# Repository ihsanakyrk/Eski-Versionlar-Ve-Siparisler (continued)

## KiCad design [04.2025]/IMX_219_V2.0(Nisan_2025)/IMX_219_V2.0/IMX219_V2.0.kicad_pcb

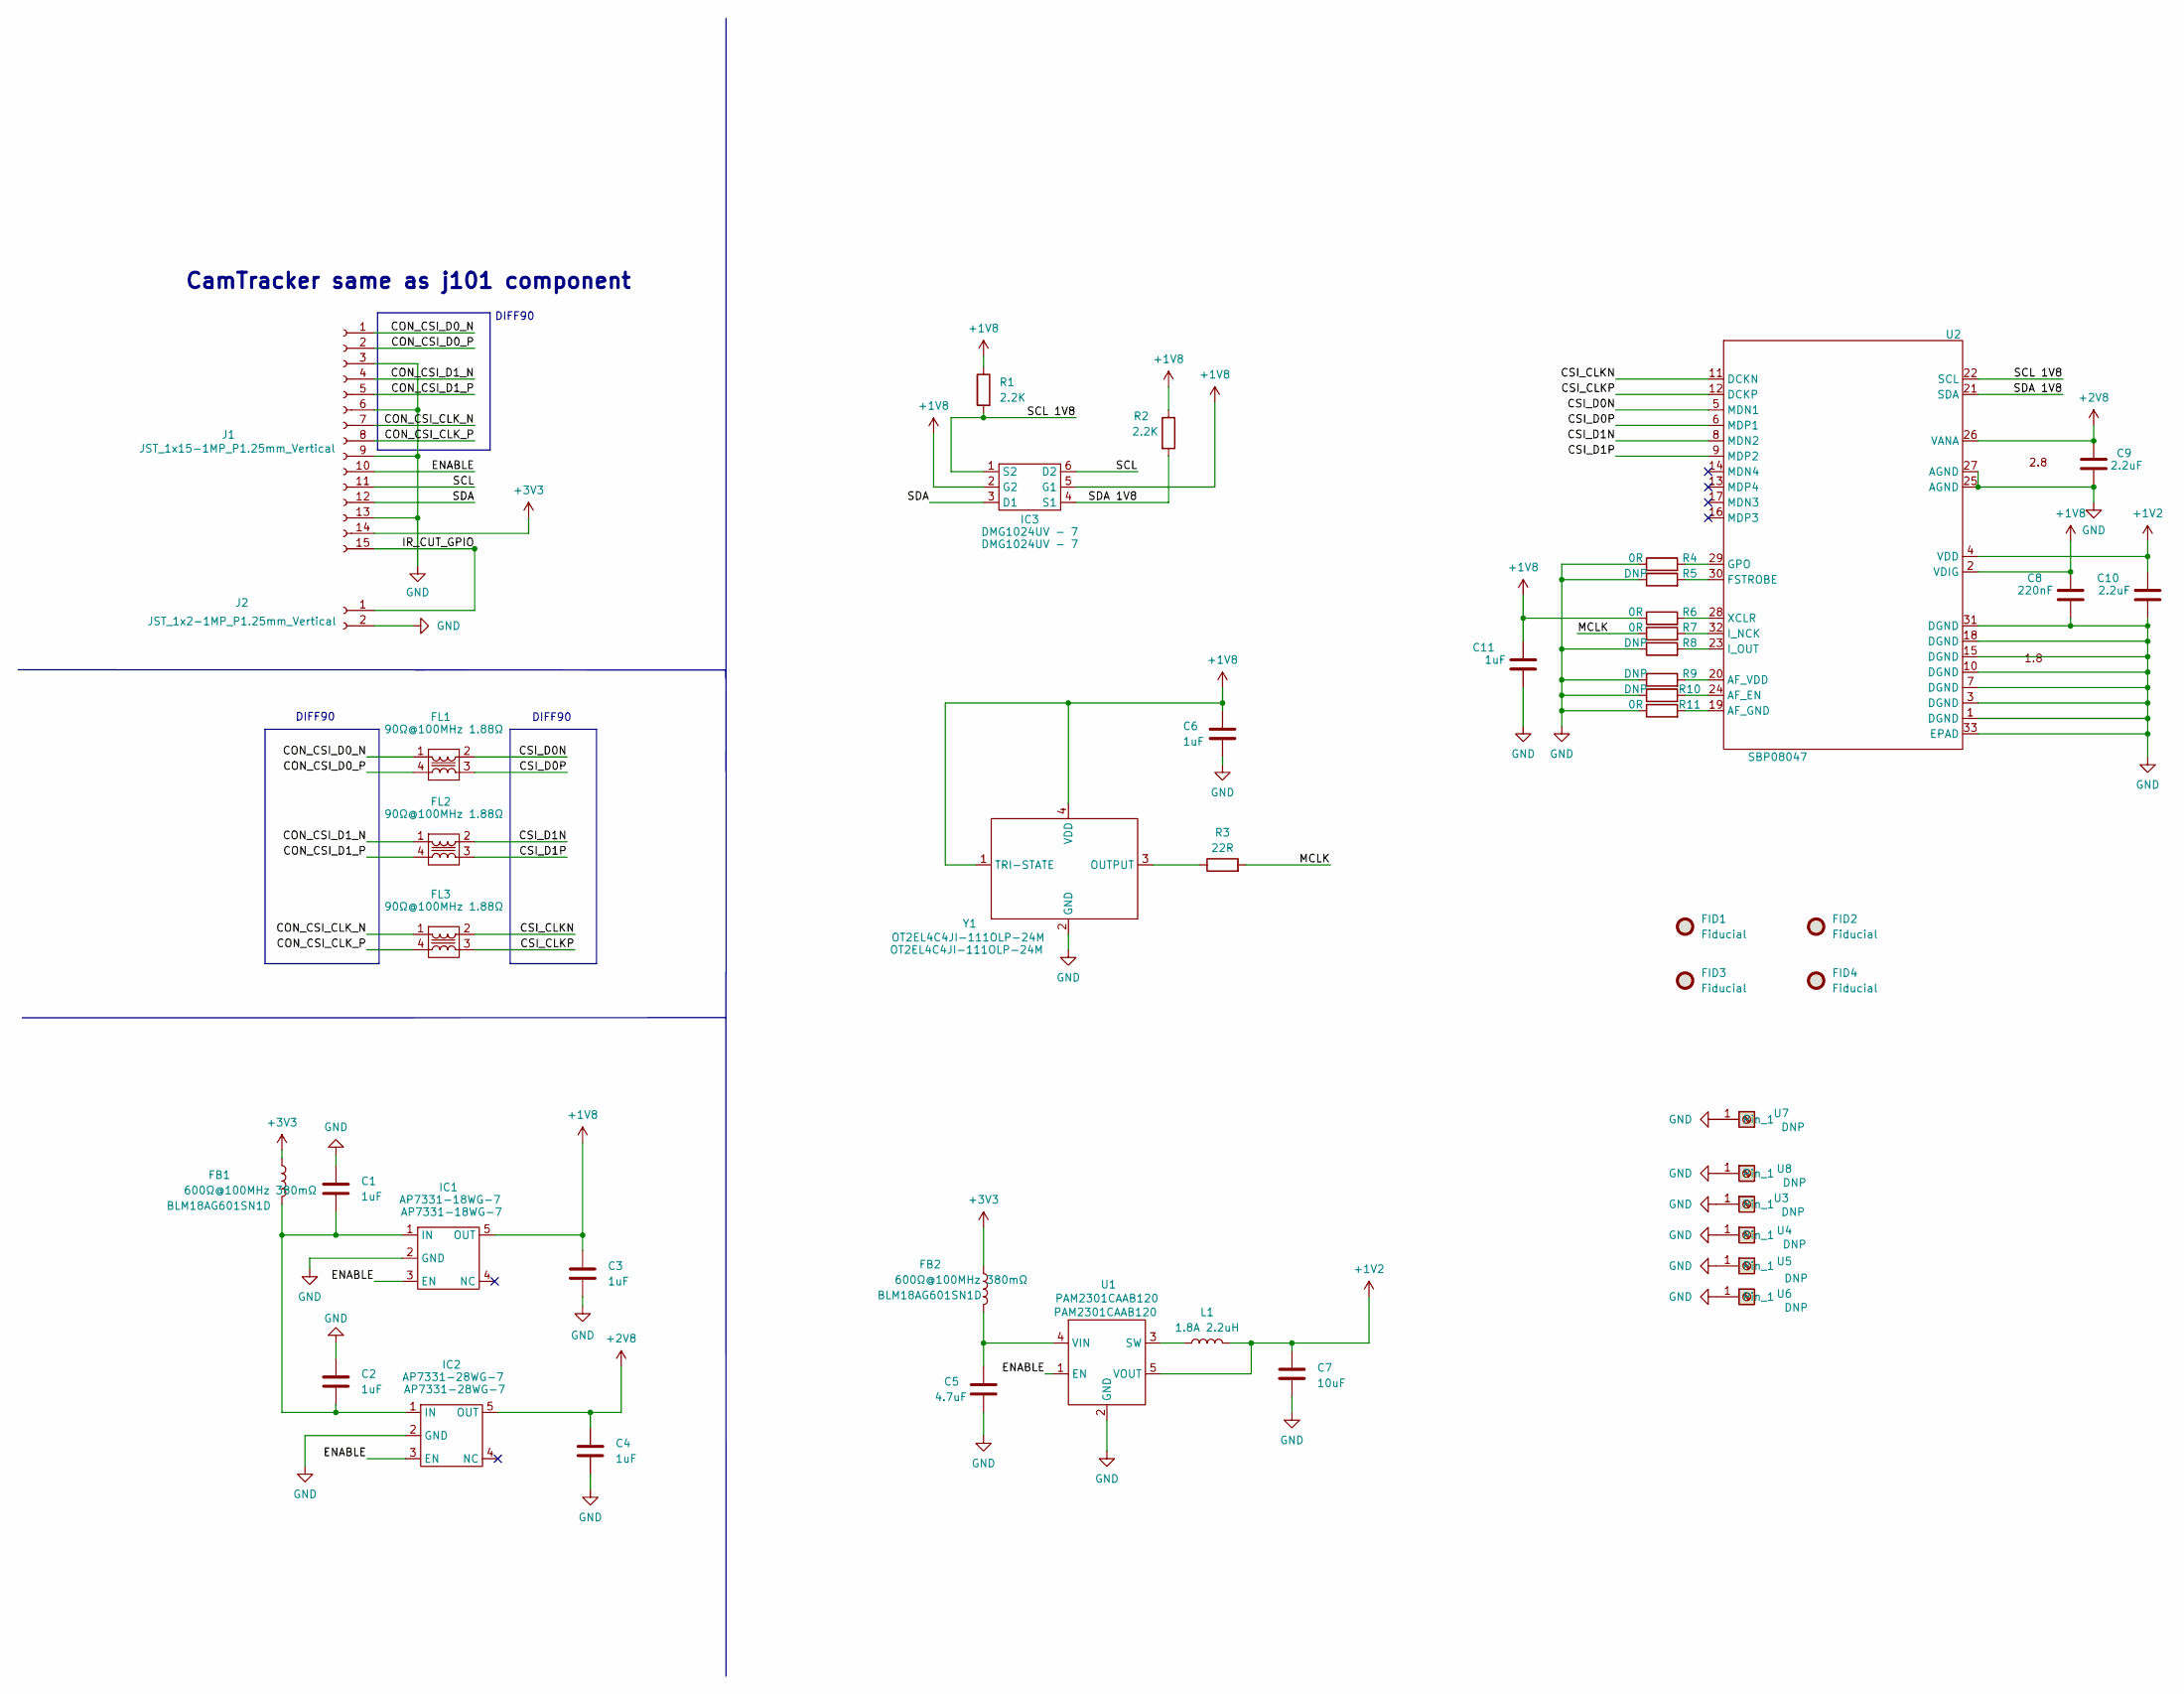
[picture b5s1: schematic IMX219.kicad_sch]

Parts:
C1, C2, C3, C4, C6: 1uF; C_0402_1005Metric; MPN CL05A105KP5NNNC
C5: 4.7uF; C_0603_1608Metric; MPN CL10A475KO8NNNC
C7: 10uF; C_0805_2012Metric; MPN CL21A106KAYNNNE
C8: 220nF; C_0402_1005Metric; MPN 0402B224K160NT
C9, C10: 2.2uF; C_0402_1005Metric; MPN CL05A225MQ5NSNC
C11: 1uF; C_0402_1005Metric
FB1, FB2: 600Ω@100MHz 380mΩ; BLM18SP221SN1B; MPN BLM18AG601SN1D
FID1, FID2, FID3, FID4: Fiducial; Fiducial_0.5mm_Mask1mm
FL1, FL2, FL3: 90Ω@100MHz 1.88Ω; DLP11SN900HL2L; MPN DLP11SN900HL2L
IC1: AP7331-18WG-7; AP7331; MPN AP7331-18WG-7
IC2: AP7331-28WG-7; AP7331; MPN AP7331-28WG-7
IC3: DMG1024UV - 7; SOT-563; MPN DMG1024UV - 7
J1: JST_1x15-1MP_P1.25mm_Vertical; MPN 1.25mm间距 立贴 1*15p
J2: JST_1x2-1MP_P1.25mm_Vertical; Con_2Ways_1.25mm; MPN p=1.25 1*3p
L1: 1.8A 2.2uH; L_1008_2520Metric; MPN IFSC1008ABER2R2M01
R1, R2: 2.2K; R_0402_1005Metric; MPN 0402WGF2201TCE
R3: 22R; R_0402_1005Metric; MPN 0402WGF220JTCE
R4, R7: 0R; R_0402_1005Metric; MPN RC-02000FT
R5, R8, R9, R10: DNP; R_0402_1005Metric; MPN DNP
R6, R11: 0R; R_0402_1005Metric
U1: PAM2301CAAB120; SOT-23-5; MPN PAM2301CAAB120
U2: SBP08047; MPN SBP08047
U3, U4, U5, U6, U7, U8: DNP; Screw Terminal Shinbo_2; MPN DNP
Y1: OT2EL4C4JI-111OLP-24M; MPN OT2EL4C4JI-111OLP-24M

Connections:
+1V2: C7.1, C10.2, L1.2, U1.5 (VOUT), U2.4 (VDD)
+1V8: C3.1, C6.1, C8.2, C11.2, IC1.5 (OUT), IC3.2 (G2), IC3.5 (G1), R1.1, R2.1, R6.1, U2.2 (VDIG), Y1.1 (TRI-STATE), Y1.4 (VDD)
+2V8: C4.1, C9.2, IC2.5 (OUT), U2.26 (VANA)
+3V3: FB1.1, FB2.1, J1.14
/IMX219/CON_CSI_CLK_N: FL3.1, J1.7
/IMX219/CON_CSI_CLK_P: FL3.4, J1.8
/IMX219/CON_CSI_D0_N: FL1.1, J1.1
/IMX219/CON_CSI_D0_P: FL1.4, J1.2
/IMX219/CON_CSI_D1_N: FL2.1, J1.4
/IMX219/CON_CSI_D1_P: FL2.4, J1.5
/IMX219/CSI_CLKN: FL3.2, U2.11 (DCKN)
/IMX219/CSI_CLKP: FL3.3, U2.12 (DCKP)
/IMX219/CSI_D0N: FL1.2, U2.5 (MDN1)
/IMX219/CSI_D0P: FL1.3, U2.6 (MDP1)
/IMX219/CSI_D1N: FL2.2, U2.8 (MDN2)
/IMX219/CSI_D1P: FL2.3, U2.9 (MDP2)
/IMX219/ENABLE: IC1.3 (EN), IC2.3 (EN), J1.10, U1.1 (EN)
/IMX219/IR_CUT_GPIO: J1.15, J2.1
/IMX219/MCLK: R3.2, R7.1
/IMX219/SCL: IC3.6 (D2), J1.11
/IMX219/SCL 1V8: IC3.1 (S2), R1.2, U2.22 (SCL)
/IMX219/SDA: IC3.3 (D1), J1.12
/IMX219/SDA 1V8: IC3.4 (S1), R2.2, U2.21 (SDA)
GND: C1.1, C2.1, C3.2, C4.2, C5.2, C6.2, C7.2, C8.1, C9.1, C10.1, C11.1, IC1.2 (GND), IC2.2 (GND), J1.3, J1.6, J1.9, J1.13, J2.2, R4.1, R5.1, R8.1, R9.1, R10.1, R11.1, U1.2 (GND), U2.1 (DGND), U2.3 (DGND), U2.7 (DGND), U2.10 (DGND), U2.15 (DGND), U2.18 (DGND), U2.25 (AGND), U2.27 (AGND), U2.31 (DGND), U2.33 (EPAD), U3.1, U4.1, U5.1, U6.1, U7.1, U8.1, Y1.2 (GND)
unnamed: C1.2, C2.2, FB1.2, IC1.1 (IN), IC2.1 (IN)
unnamed: L1.1, U1.3 (SW)
unnamed: C5.1, FB2.2, U1.4 (VIN)
unnamed: R10.2, U2.24 (AF_EN)
unnamed: R11.2, U2.19 (AF_GND)
unnamed: R9.2, U2.20 (AF_VDD)
unnamed: R5.2, U2.30 (FSTROBE)
unnamed: R4.2, U2.29 (GPO)
unnamed: R7.2, U2.32 (I_NCK)
unnamed: R8.2, U2.23 (I_OUT)
unnamed: R6.2, U2.28 (XCLR)
unnamed: R3.1, Y1.3 (OUTPUT)

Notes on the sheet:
DIFF90
CamTracker same as j101 component

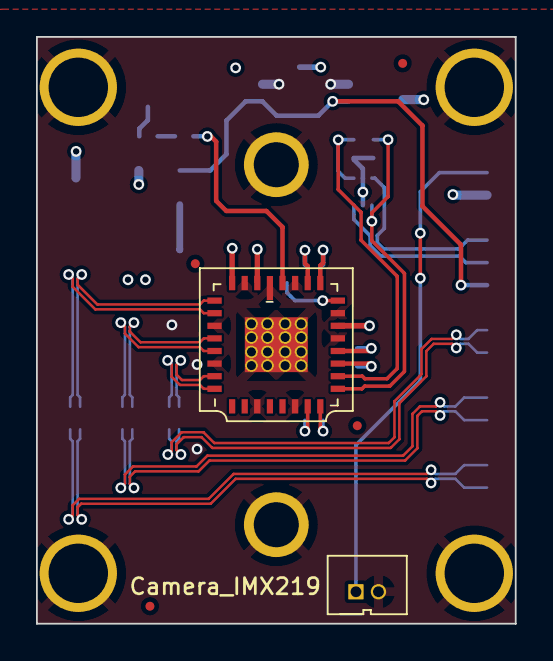
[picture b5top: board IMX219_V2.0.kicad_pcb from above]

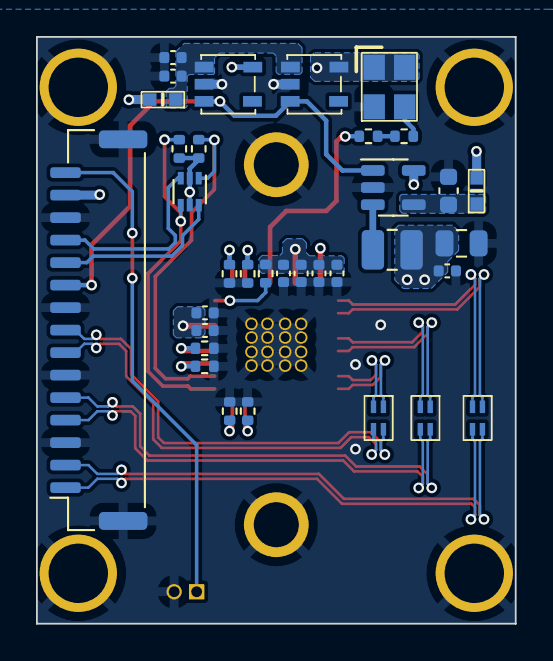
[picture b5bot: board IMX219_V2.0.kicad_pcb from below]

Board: 4 copper layers, 26.6 x 32.6 mm, 46 parts (34 on the bottom side), 36 nets.

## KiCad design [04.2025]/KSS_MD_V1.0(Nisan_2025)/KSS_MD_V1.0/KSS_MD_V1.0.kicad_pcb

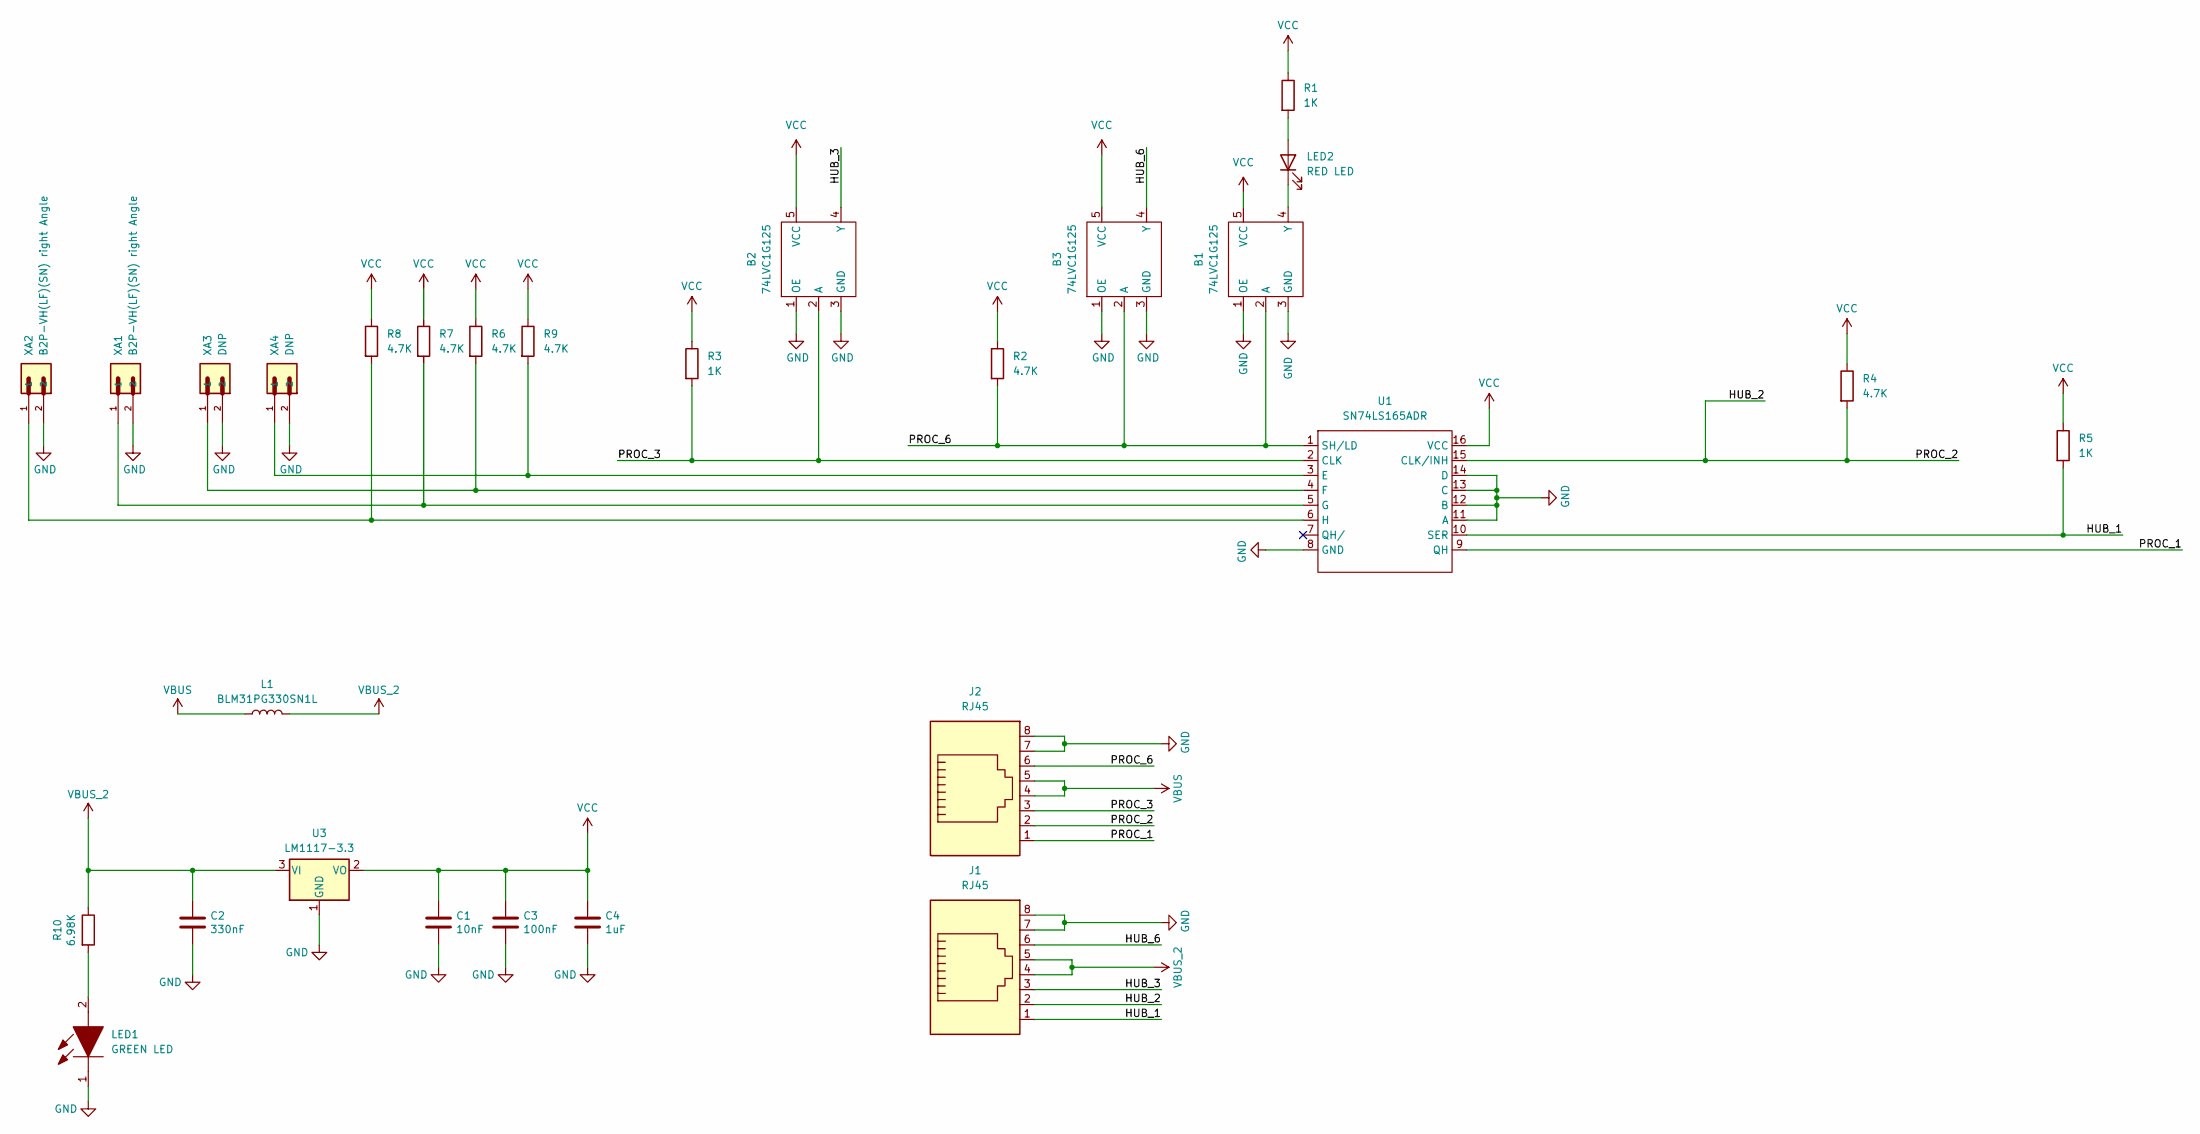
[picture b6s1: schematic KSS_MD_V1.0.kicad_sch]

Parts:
B1, B2, B3: 74LVC1G125; SOT-353_SC-70-5
C1: 10nF; C_0603_1608Metric
C2: 330nF; C_0603_1608Metric
C3: 100nF; C_0603_1608Metric
C4: 1uF; C_0603_1608Metric
J1, J2: RJ45; RJ45_OST_PJ012-8P8CX_Vertical
L1: BLM31PG330SN1L; L_1206_3216Metric; MPN BLM31PG330SN1L
LED1: GREEN LED; LED_0805_2012Metric
LED2: RED LED; LED_0805_2012Metric
R1, R3, R5: 1K; R_0603_1608Metric
R2, R4, R6, R7, R8, R9: 4.7K; R_0603_1608Metric
R10: 6.98K; R_0603_1608Metric
U1: SN74LS165ADR; SOIC-16_3.9x9.9mm_P1.27mm
U3: LM1117-3.3; SOT-223-3_TabPin2
XA1, XA2: B2P-VH(LF)(SN) right Angle; Hirose_DF63M-2P-3.96DSA_1x02_P3.96mm_Vertical
XA3, XA4: DNP; Hirose_DF63M-2P-3.96DSA_1x02_P3.96mm_Vertical

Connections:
/HUB_1: J1.1, R5.2, U1.10 (SER)
/HUB_2: J1.2, J2.2, R4.2, U1.15 (CLK/INH)
/HUB_3: B2.4 (Y), J1.3
/HUB_6: B3.4 (Y), J1.6
/PROC_1: J2.1, U1.9 (QH)
/PROC_3: B2.2 (A), J2.3, R3.2, U1.2 (CLK)
/PROC_6: B1.2 (A), B3.2 (A), J2.6, R2.2, U1.1 (SH/LD)
GND: B1.1 (OE), B1.3 (GND), B2.1 (OE), B2.3 (GND), B3.1 (OE), B3.3 (GND), C1.2, C2.2, C3.2, C4.2, J1.7, J1.8, J2.7, J2.8, LED1.1, U1.8 (GND), U1.11 (A), U1.12 (B), U1.13 (C), U1.14 (D), U3.1 (GND), XA1.2, XA2.2, XA3.2, XA4.2
unnamed: B1.4 (Y), LED2.1 (K)
unnamed: LED1.2, R10.2
unnamed: LED2.2 (A), R1.2
unnamed: R9.2, U1.3 (E), XA4.1
unnamed: R6.2, U1.4 (F), XA3.1
unnamed: R7.2, U1.5 (G), XA1.1
unnamed: R8.2, U1.6 (H), XA2.1
VBUS: J2.4, J2.5, L1.1
VBUS_2: C2.1, J1.4, J1.5, L1.2, R10.1, U3.3 (VI)
VCC: B1.5 (VCC), B2.5 (VCC), B3.5 (VCC), C1.1, C3.1, C4.1, R1.1, R2.1, R3.1, R4.1, R5.1, R6.1, R7.1, R8.1, R9.1, U1.16 (VCC), U3.2 (VO)

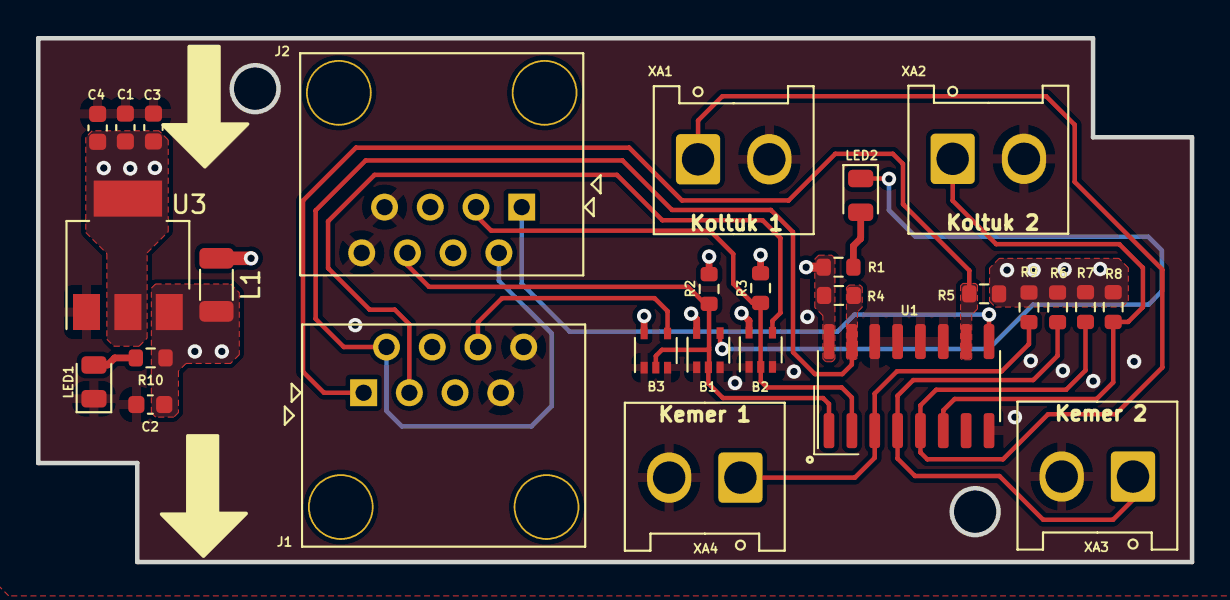
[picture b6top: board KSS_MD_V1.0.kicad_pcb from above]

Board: 2 copper layers, 64.1 x 29.1 mm, 28 parts (0 on the bottom side), 18 nets.
